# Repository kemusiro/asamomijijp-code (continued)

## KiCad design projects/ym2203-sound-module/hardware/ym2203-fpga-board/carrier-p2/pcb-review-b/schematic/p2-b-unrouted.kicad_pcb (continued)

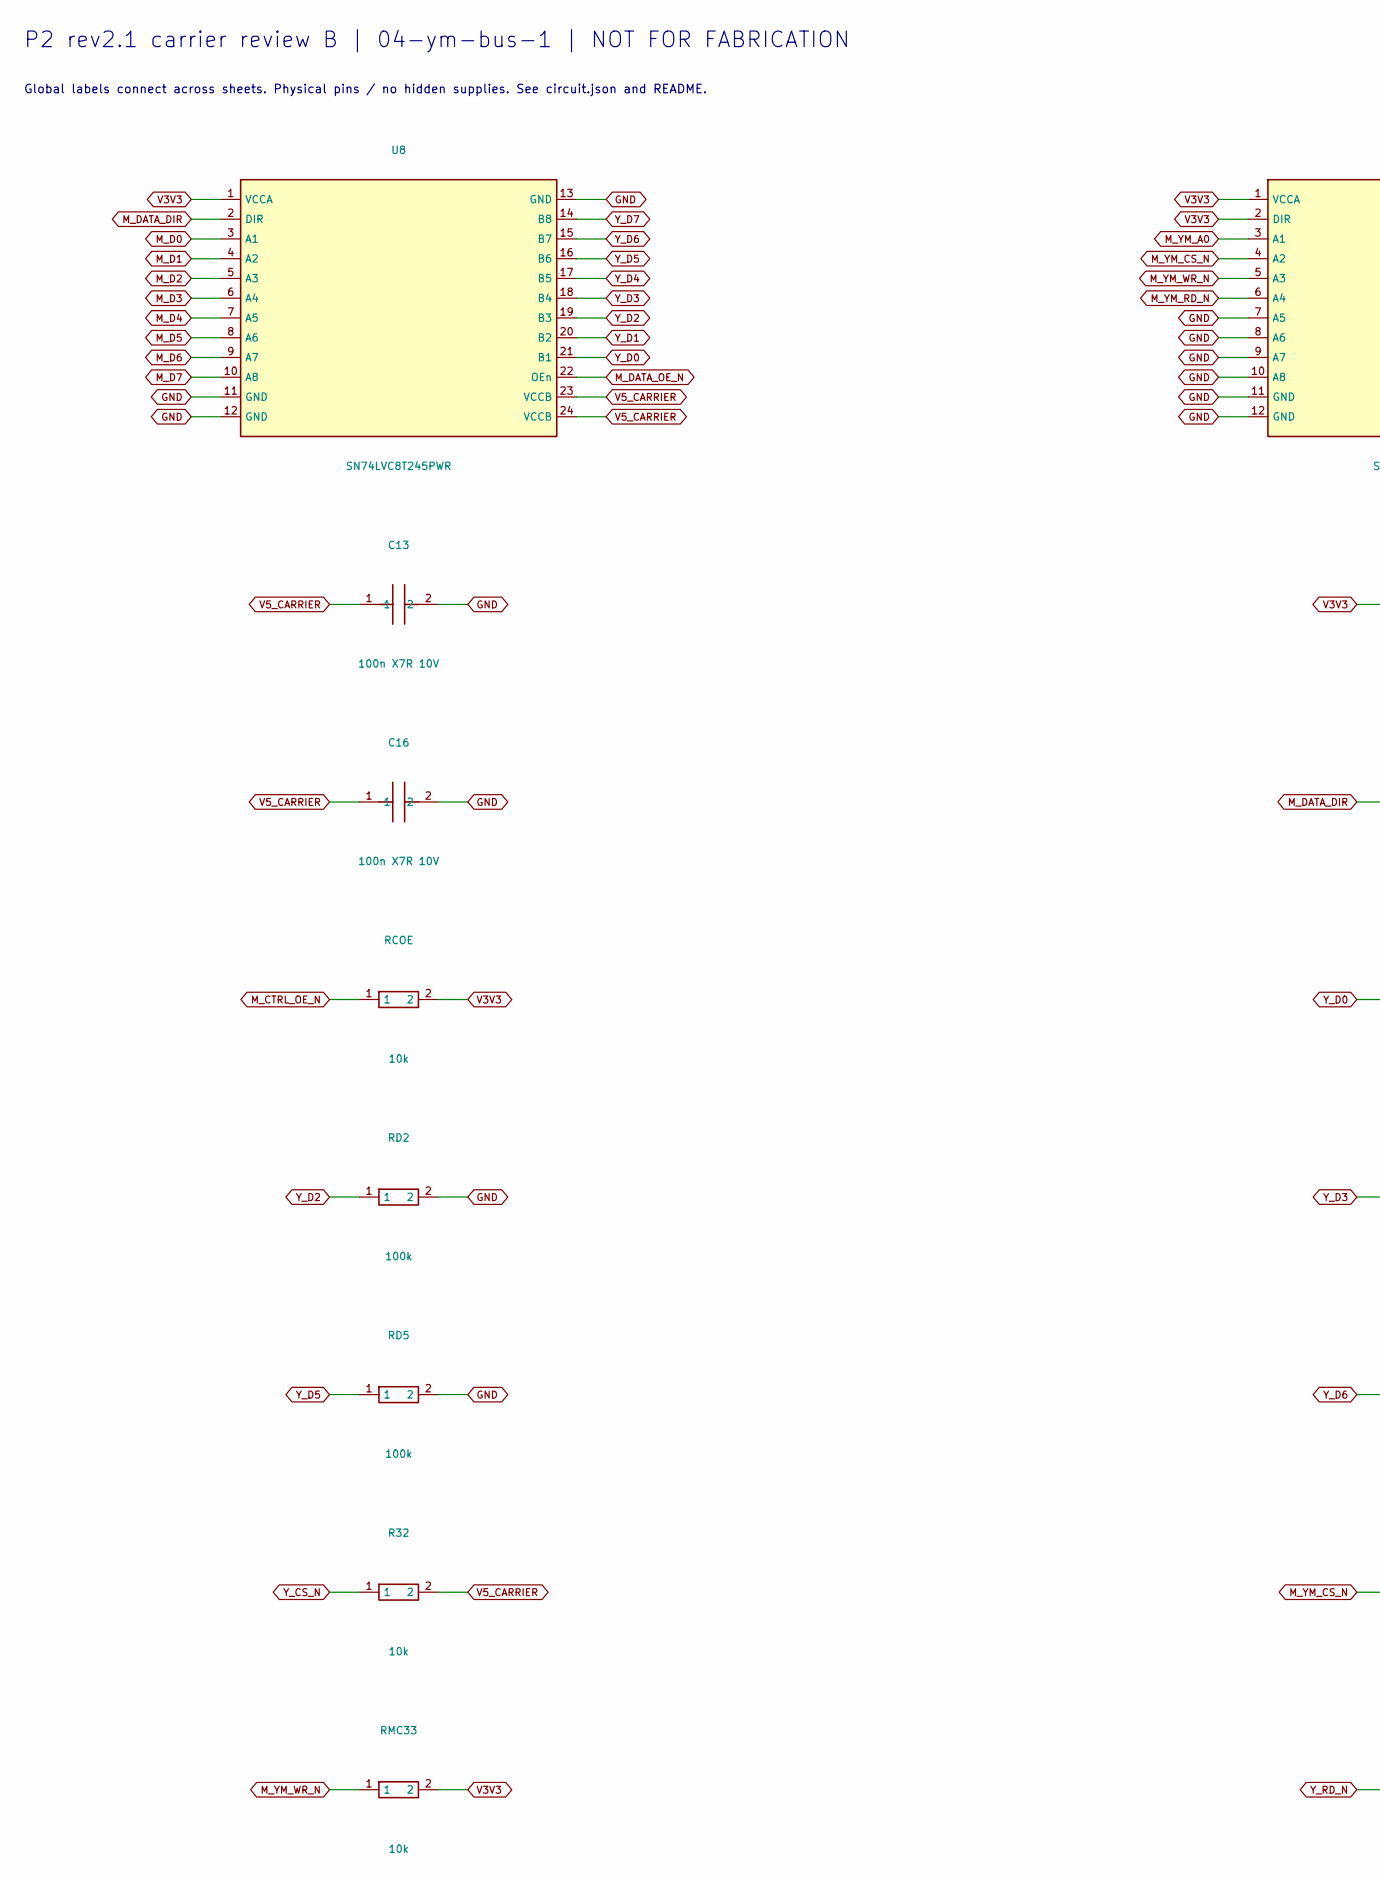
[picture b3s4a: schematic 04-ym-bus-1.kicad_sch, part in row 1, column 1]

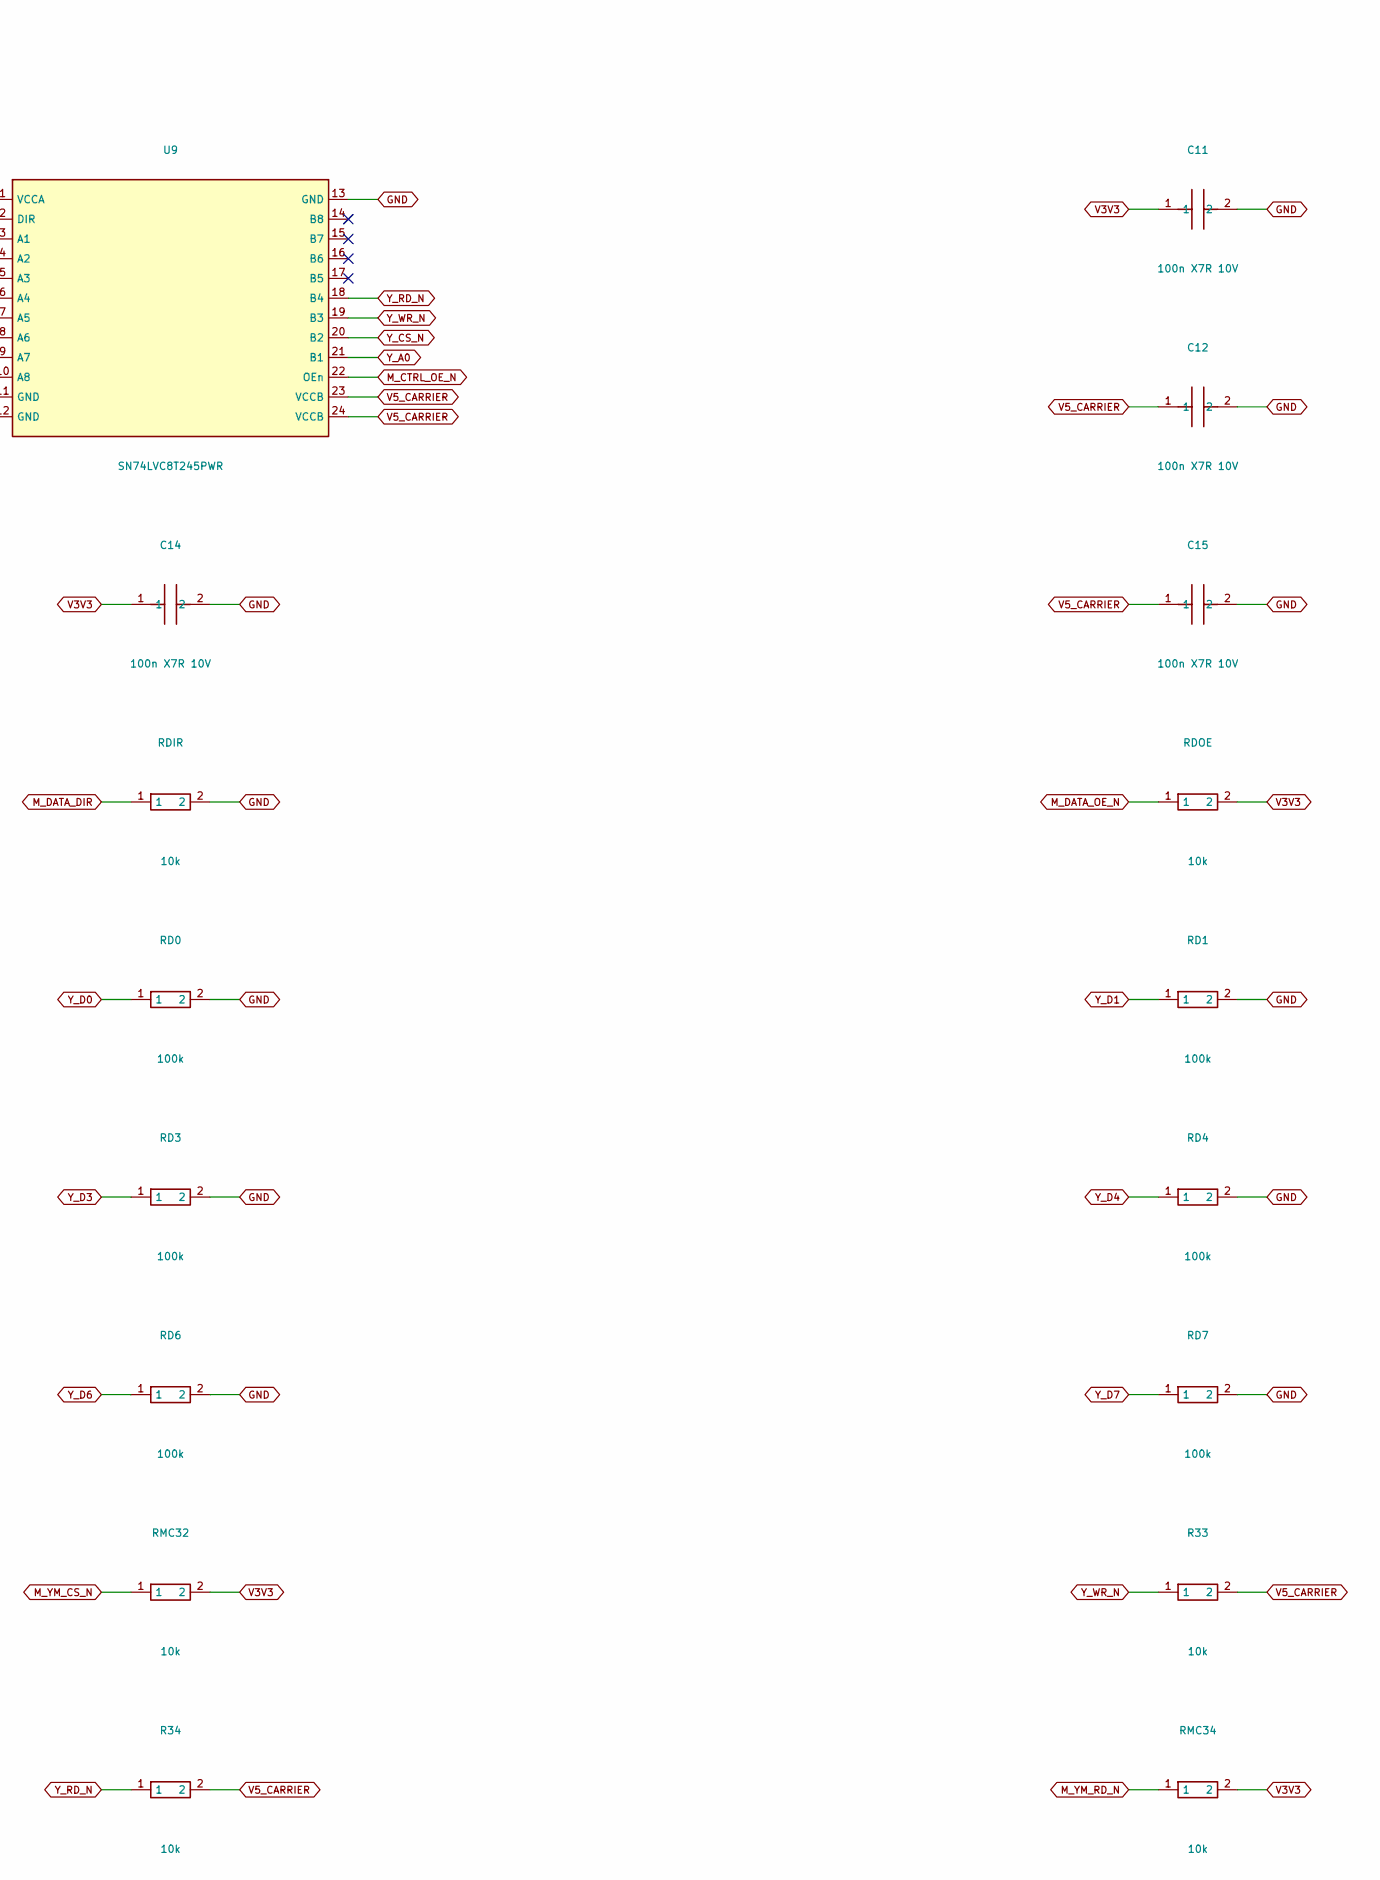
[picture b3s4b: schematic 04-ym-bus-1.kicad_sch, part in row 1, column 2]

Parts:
C11, C12, C13, C14, C15, C16: 100n X7R 10V; C_0805_2012Metric
R32, R33, R34: 10k; R_0805_2012Metric
RCOE: 10k; R_0805_2012Metric
RD0, RD1, RD2, RD3, RD4, RD5, RD6, RD7: 100k; R_0805_2012Metric
RDIR: 10k; R_0805_2012Metric
RDOE: 10k; R_0805_2012Metric
RMC32, RMC33, RMC34: 10k; R_0805_2012Metric
U8, U9: SN74LVC8T245PWR; TSSOP-24_4.4x7.8mm_P0.65mm

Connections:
GND: C11.2, C12.2, C13.2, C14.2, C15.2, C16.2, RD0.2, RD1.2, RD2.2, RD3.2, RD4.2, RD5.2, RD6.2, RD7.2, RDIR.2, U8.11 (GND), U8.12 (GND), U8.13 (GND), U9.7 (A5), U9.8 (A6), U9.9 (A7), U9.10 (A8), U9.11 (GND), U9.12 (GND), U9.13 (GND); also elsewhere on the board
M_CTRL_OE_N: RCOE.1, U9.22 (OEn); also elsewhere on the board
M_D0: U8.3 (A1); also elsewhere on the board
M_D1: U8.4 (A2); also elsewhere on the board
M_D2: U8.5 (A3); also elsewhere on the board
M_D3: U8.6 (A4); also elsewhere on the board
M_D4: U8.7 (A5); also elsewhere on the board
M_D5: U8.8 (A6); also elsewhere on the board
M_D6: U8.9 (A7); also elsewhere on the board
M_D7: U8.10 (A8); also elsewhere on the board
M_DATA_DIR: RDIR.1, U8.2 (DIR); also elsewhere on the board
M_DATA_OE_N: RDOE.1, U8.22 (OEn); also elsewhere on the board
M_YM_A0: U9.3 (A1); also elsewhere on the board
M_YM_CS_N: RMC32.1, U9.4 (A2); also elsewhere on the board
M_YM_RD_N: RMC34.1, U9.6 (A4); also elsewhere on the board
M_YM_WR_N: RMC33.1, U9.5 (A3); also elsewhere on the board
V3V3: C11.1, C14.1, RCOE.2, RDOE.2, RMC32.2, RMC33.2, RMC34.2, U8.1 (VCCA), U9.1 (VCCA), U9.2 (DIR); also elsewhere on the board
V5_CARRIER: C12.1, C13.1, C15.1, C16.1, R32.2, R33.2, R34.2, U8.23 (VCCB), U8.24 (VCCB), U9.23 (VCCB), U9.24 (VCCB); also elsewhere on the board
Y_A0: U9.21 (B1); also elsewhere on the board
Y_CS_N: R32.1, U9.20 (B2); also elsewhere on the board
Y_D0: RD0.1, U8.21 (B1); also elsewhere on the board
Y_D1: RD1.1, U8.20 (B2); also elsewhere on the board
Y_D2: RD2.1, U8.19 (B3); also elsewhere on the board
Y_D3: RD3.1, U8.18 (B4); also elsewhere on the board
Y_D4: RD4.1, U8.17 (B5); also elsewhere on the board
Y_D5: RD5.1, U8.16 (B6); also elsewhere on the board
Y_D6: RD6.1, U8.15 (B7); also elsewhere on the board
Y_D7: RD7.1, U8.14 (B8); also elsewhere on the board
Y_RD_N: R34.1, U9.18 (B4); also elsewhere on the board
Y_WR_N: R33.1, U9.19 (B3); also elsewhere on the board

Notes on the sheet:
P2 rev2.1 carrier review B | 04-ym-bus-1 | NOT FOR FABRICATION
Global labels connect across sheets. Physical pins / no hidden supplies. See circuit.json and README.

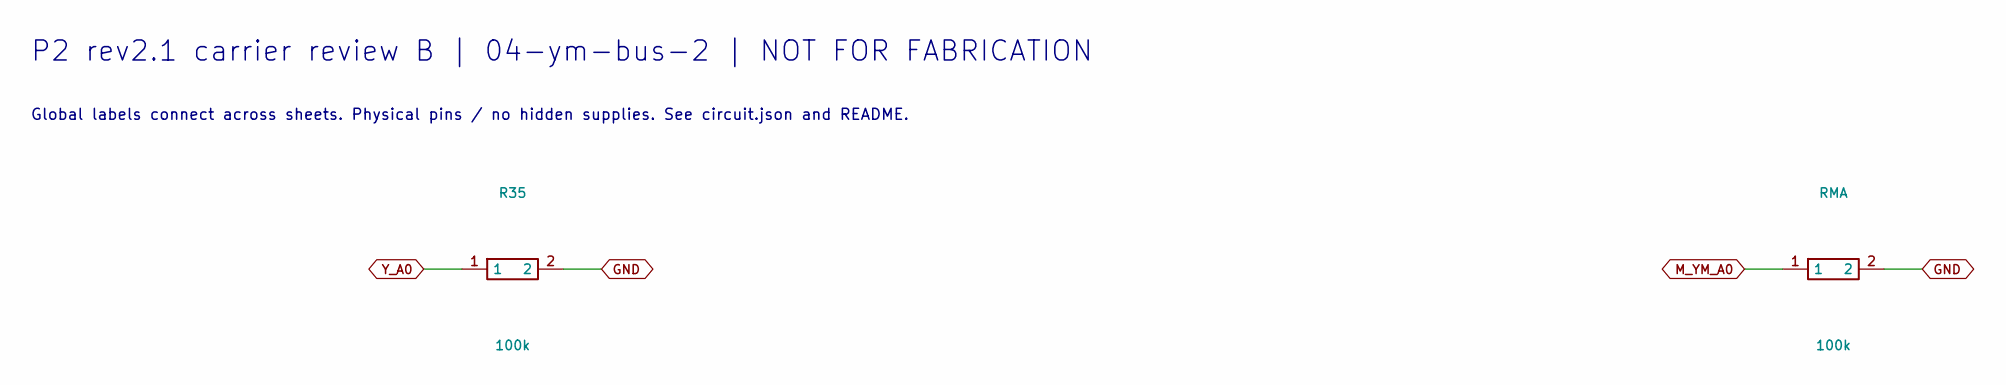
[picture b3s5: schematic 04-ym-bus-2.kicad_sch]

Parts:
R35: 100k; R_0805_2012Metric
RMA: 100k; R_0805_2012Metric

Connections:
GND: R35.2, RMA.2; also elsewhere on the board
M_YM_A0: RMA.1; also elsewhere on the board
Y_A0: R35.1; also elsewhere on the board

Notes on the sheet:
P2 rev2.1 carrier review B | 04-ym-bus-2 | NOT FOR FABRICATION
Global labels connect across sheets. Physical pins / no hidden supplies. See circuit.json and README.

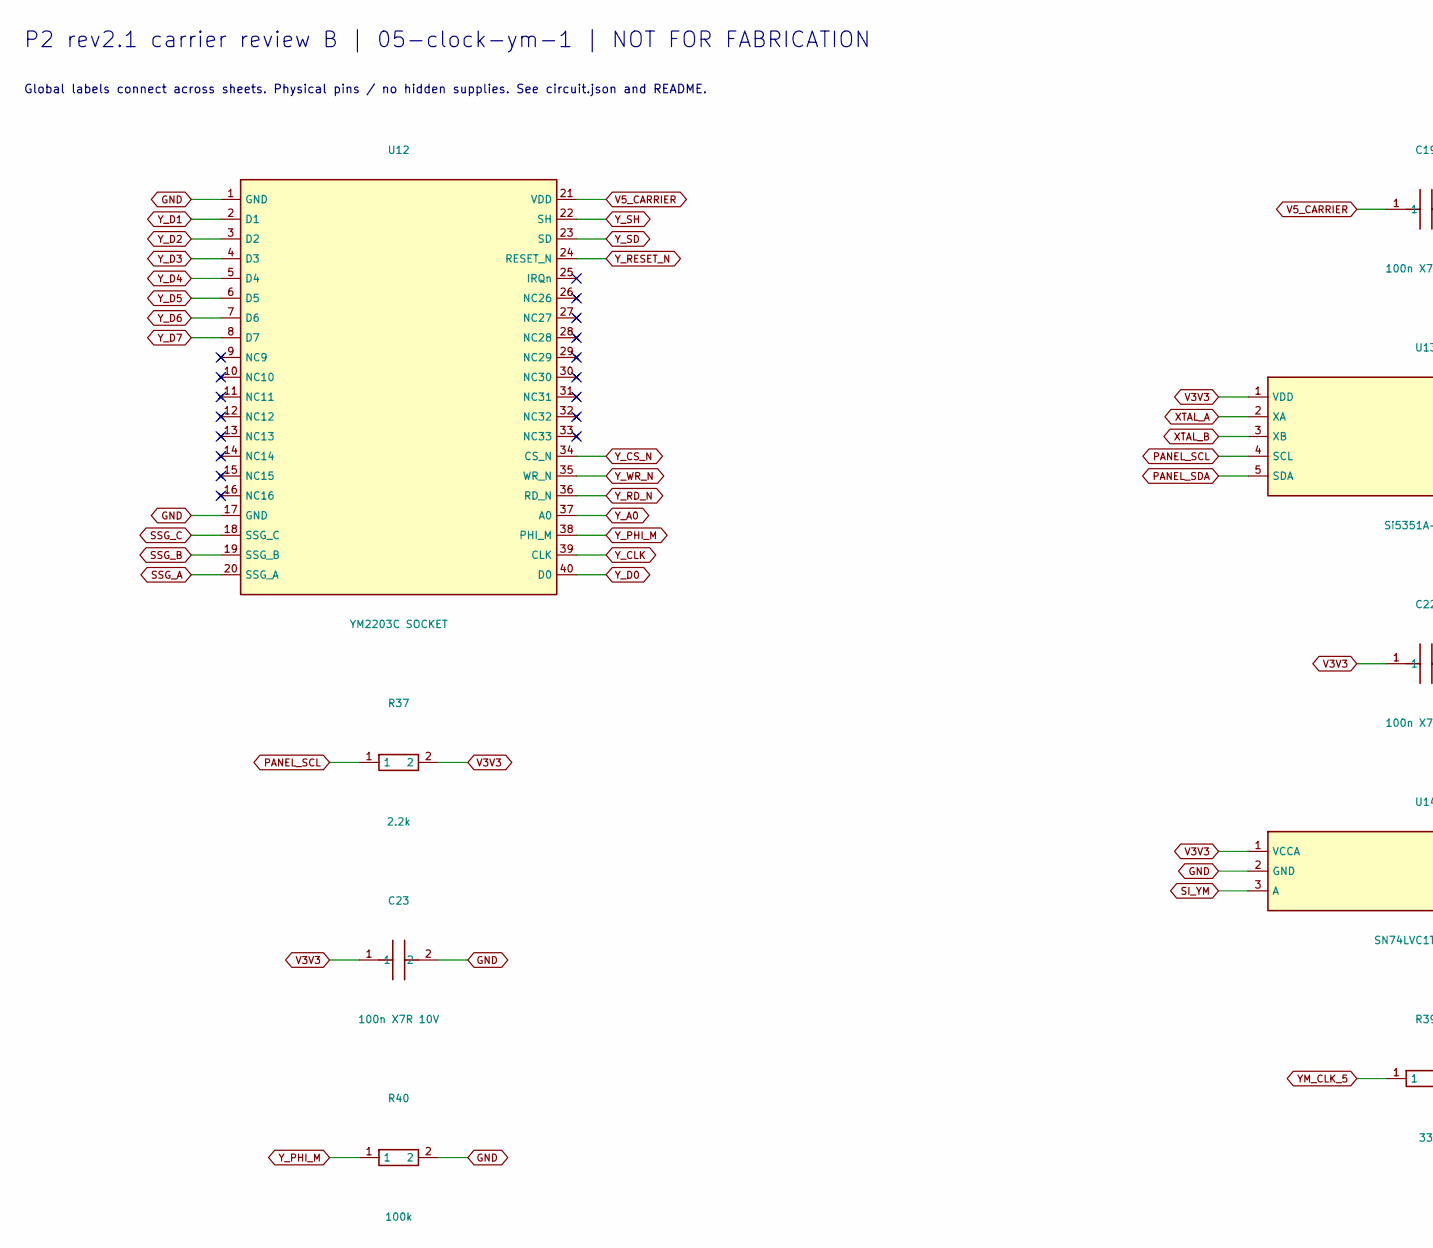
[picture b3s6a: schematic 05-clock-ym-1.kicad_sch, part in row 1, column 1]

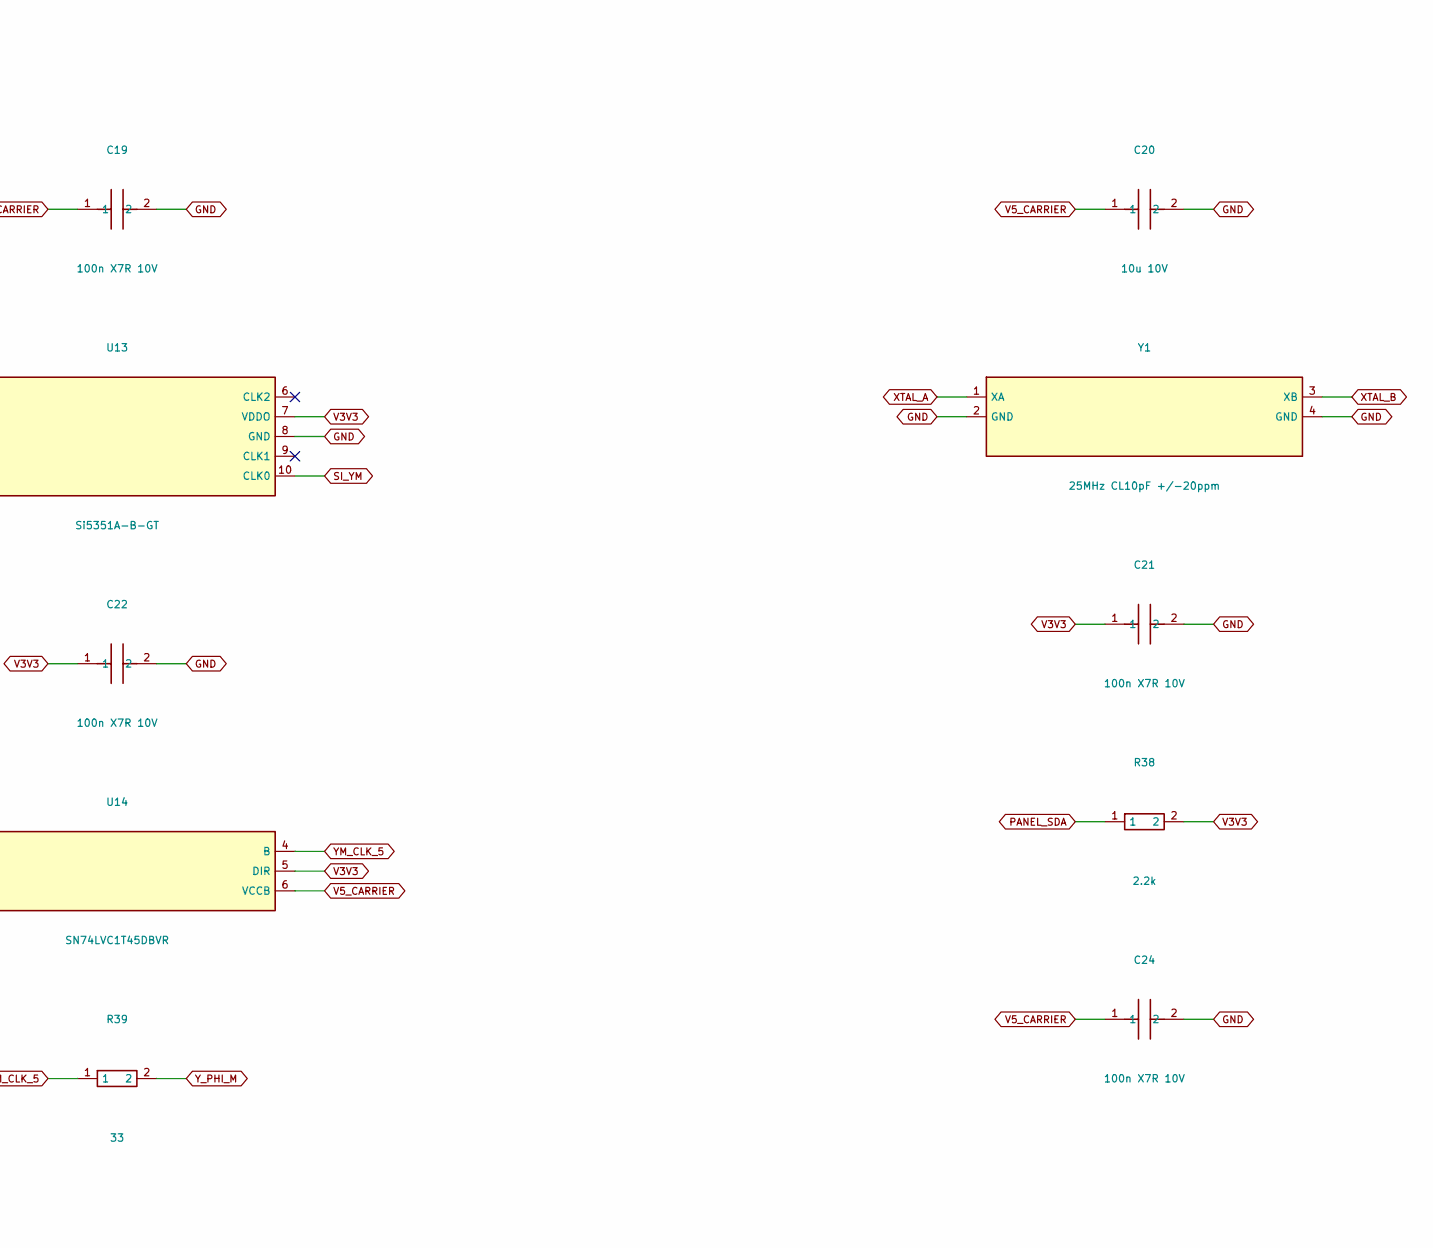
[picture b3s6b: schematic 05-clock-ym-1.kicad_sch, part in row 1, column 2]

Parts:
C19, C21, C22, C23, C24: 100n X7R 10V; C_0805_2012Metric
C20: 10u 10V; C_0805_2012Metric
R37, R38: 2.2k; R_0805_2012Metric
R39: 33; R_0805_2012Metric
R40: 100k; R_0805_2012Metric
U12: YM2203C SOCKET; DIP-40_W15.24mm_Socket
U13: Si5351A-B-GT; MSOP-10_3x3mm_P0.5mm
U14: SN74LVC1T45DBVR; SOT-23-6
Y1: 25MHz CL10pF +/-20ppm; Crystal_SMD_3225-4Pin_3.2x2.5mm

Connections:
GND: C19.2, C20.2, C21.2, C22.2, C23.2, C24.2, R40.2, U12.1 (GND), U12.17 (GND), U13.8 (GND), U14.2 (GND), Y1.2 (GND), Y1.4 (GND); also elsewhere on the board
PANEL_SCL: R37.1, U13.4 (SCL); also elsewhere on the board
PANEL_SDA: R38.1, U13.5 (SDA); also elsewhere on the board
SI_YM: U13.10 (CLK0), U14.3 (A)
SSG_A: U12.20 (SSG_A); also elsewhere on the board
SSG_B: U12.19 (SSG_B); also elsewhere on the board
SSG_C: U12.18 (SSG_C); also elsewhere on the board
V3V3: C21.1, C22.1, C23.1, R37.2, R38.2, U13.1 (VDD), U13.7 (VDDO), U14.1 (VCCA), U14.5 (DIR); also elsewhere on the board
V5_CARRIER: C19.1, C20.1, C24.1, U12.21 (VDD), U14.6 (VCCB); also elsewhere on the board
XTAL_A: U13.2 (XA), Y1.1 (XA)
XTAL_B: U13.3 (XB), Y1.3 (XB)
YM_CLK_5: R39.1, U14.4 (B)
Y_A0: U12.37 (A0); also elsewhere on the board
Y_CLK: U12.39 (CLK); also elsewhere on the board
Y_CS_N: U12.34 (CS_N); also elsewhere on the board
Y_D0: U12.40 (D0); also elsewhere on the board
Y_D1: U12.2 (D1); also elsewhere on the board
Y_D2: U12.3 (D2); also elsewhere on the board
Y_D3: U12.4 (D3); also elsewhere on the board
Y_D4: U12.5 (D4); also elsewhere on the board
Y_D5: U12.6 (D5); also elsewhere on the board
Y_D6: U12.7 (D6); also elsewhere on the board
Y_D7: U12.8 (D7); also elsewhere on the board
Y_PHI_M: R39.2, R40.1, U12.38 (PHI_M)
Y_RD_N: U12.36 (RD_N); also elsewhere on the board
Y_RESET_N: U12.24 (RESET_N); also elsewhere on the board
Y_SD: U12.23 (SD); also elsewhere on the board
Y_SH: U12.22 (SH); also elsewhere on the board
Y_WR_N: U12.35 (WR_N); also elsewhere on the board

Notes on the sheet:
P2 rev2.1 carrier review B | 05-clock-ym-1 | NOT FOR FABRICATION
Global labels connect across sheets. Physical pins / no hidden supplies. See circuit.json and README.

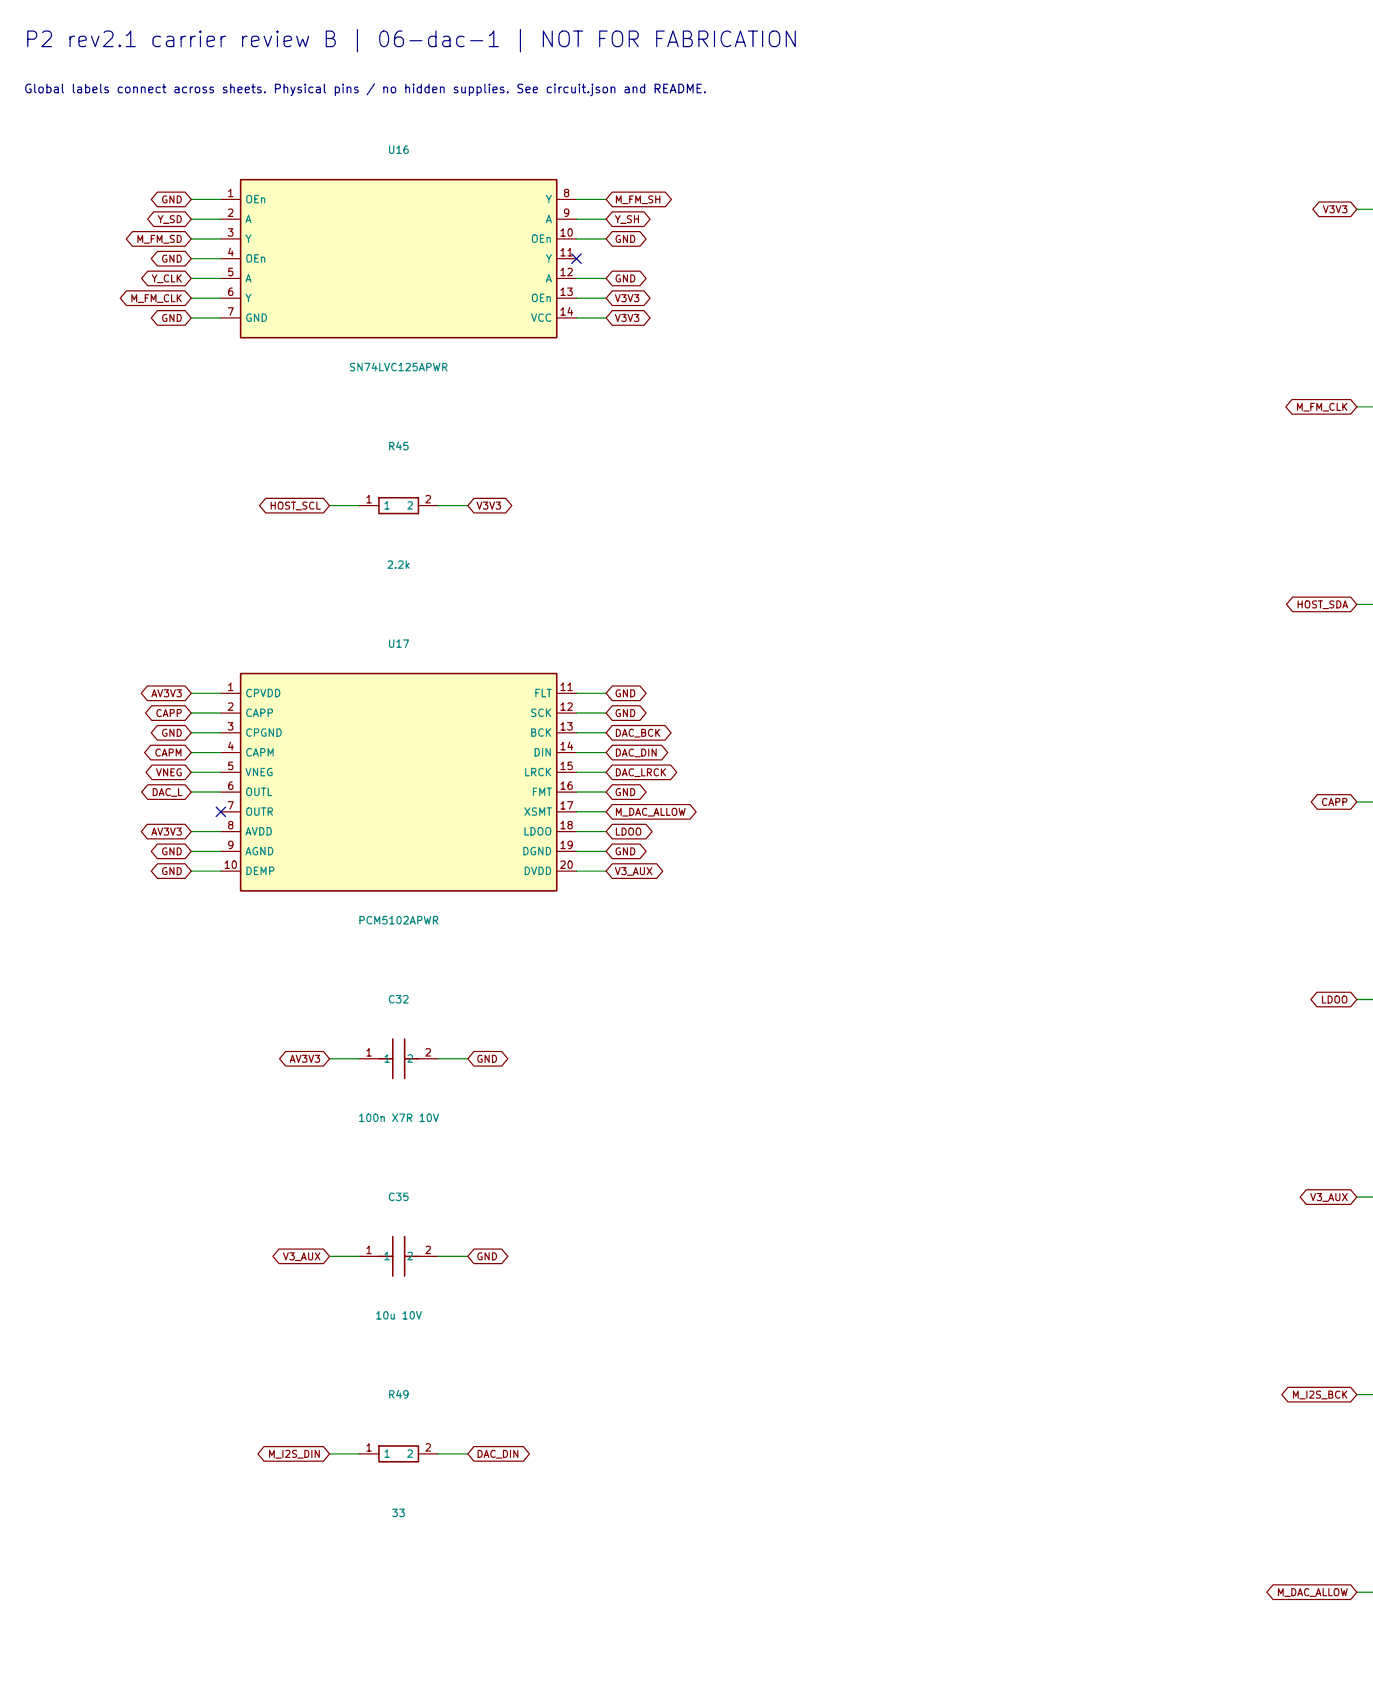
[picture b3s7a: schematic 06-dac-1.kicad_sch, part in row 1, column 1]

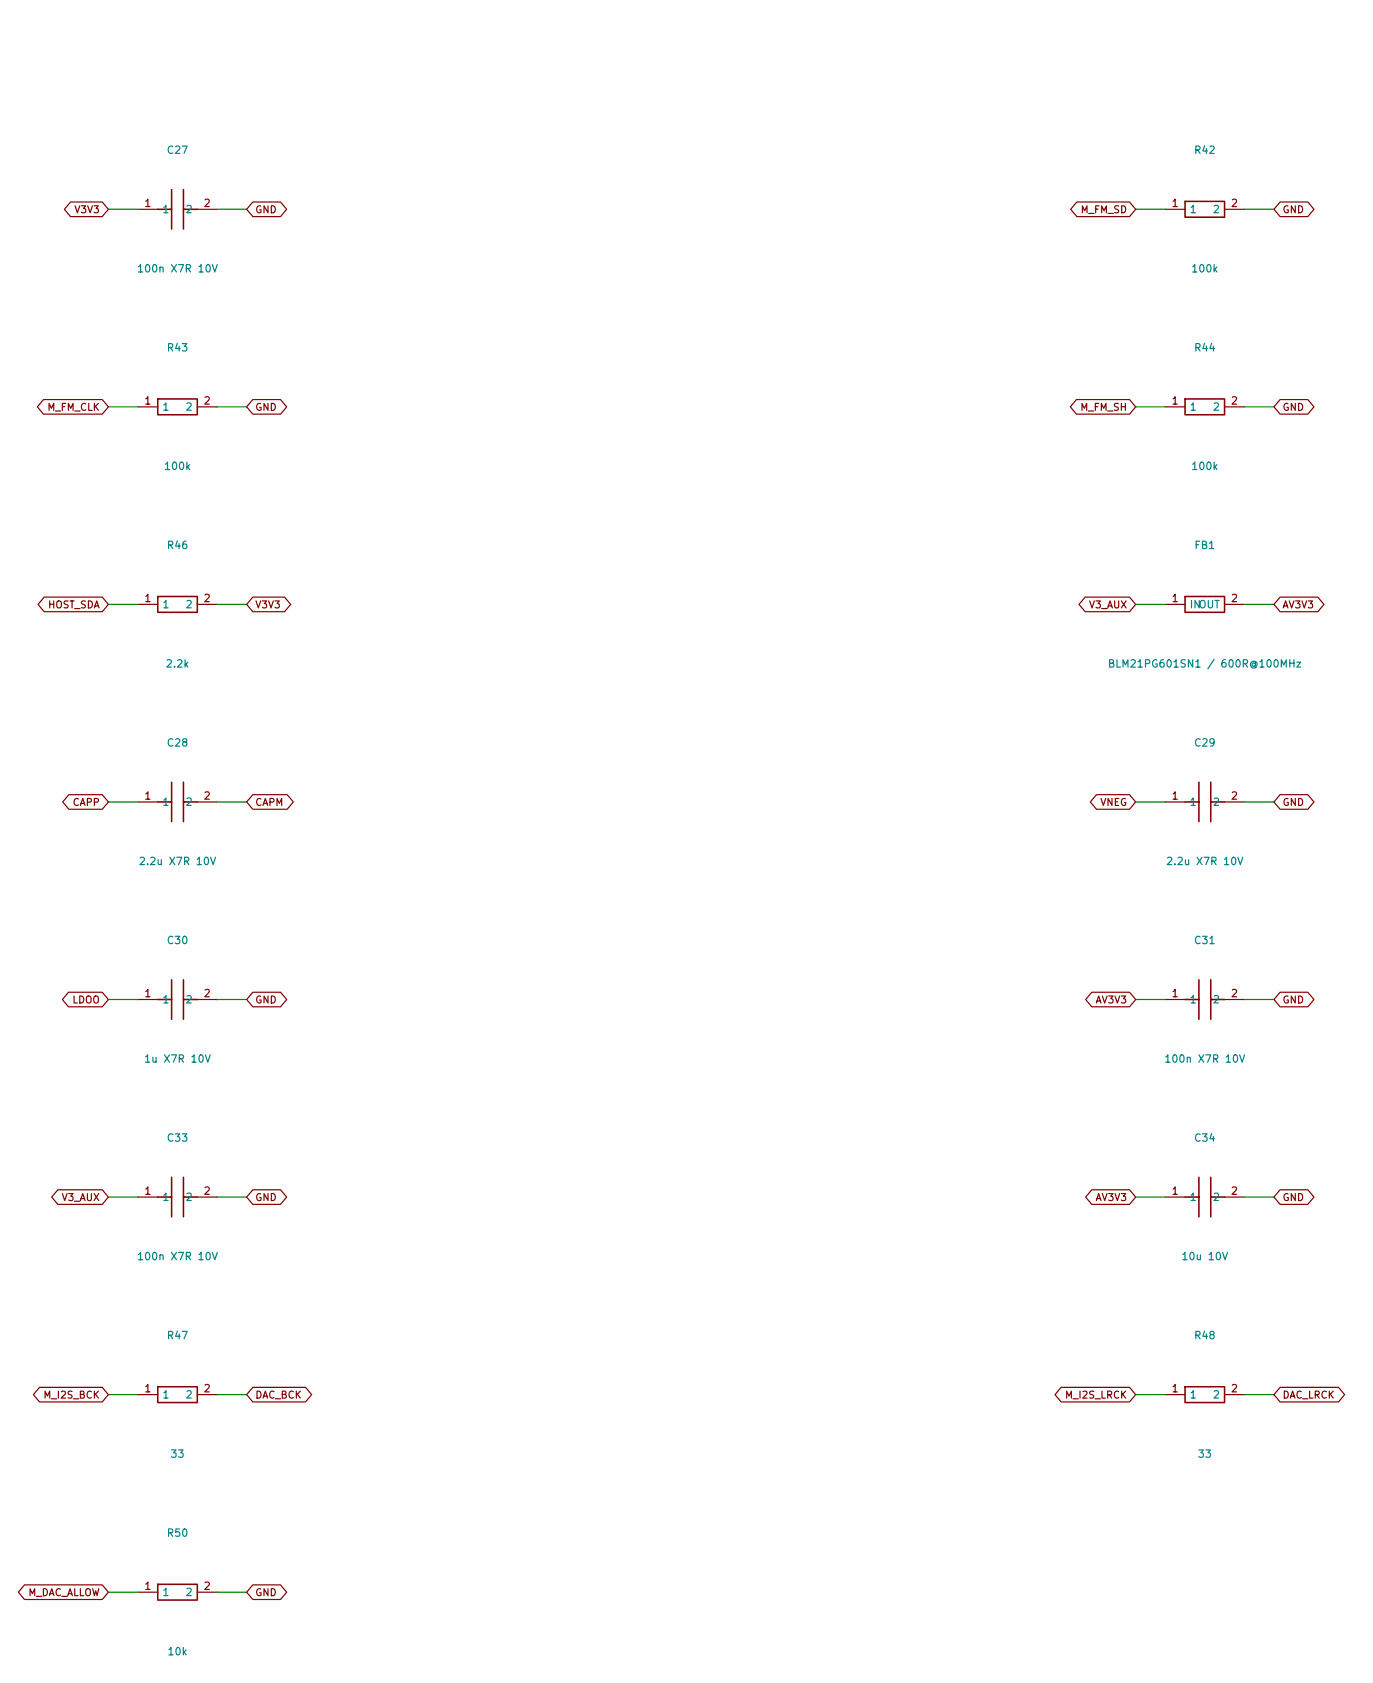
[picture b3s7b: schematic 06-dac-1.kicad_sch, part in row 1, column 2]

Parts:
C27, C31, C32, C33: 100n X7R 10V; C_0805_2012Metric
C28, C29: 2.2u X7R 10V; C_0805_2012Metric
C30: 1u X7R 10V; C_0805_2012Metric
C34, C35: 10u 10V; C_0805_2012Metric
FB1: BLM21PG601SN1 / 600R@100MHz; L_0805_2012Metric
R42, R43, R44: 100k; R_0805_2012Metric
R45, R46: 2.2k; R_0805_2012Metric
R47, R48, R49: 33; R_0805_2012Metric
R50: 10k; R_0805_2012Metric
U16: SN74LVC125APWR; TSSOP-14_4.4x5mm_P0.65mm
U17: PCM5102APWR; TSSOP-20_4.4x6.5mm_P0.65mm

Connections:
AV3V3: C31.1, C32.1, C34.1, FB1.2 (OUT), U17.1 (CPVDD), U17.8 (AVDD)
CAPM: C28.2, U17.4 (CAPM)
CAPP: C28.1, U17.2 (CAPP)
DAC_BCK: R47.2, U17.13 (BCK); also elsewhere on the board
DAC_DIN: R49.2, U17.14 (DIN); also elsewhere on the board
DAC_L: U17.6 (OUTL); also elsewhere on the board
DAC_LRCK: R48.2, U17.15 (LRCK); also elsewhere on the board
GND: C27.2, C29.2, C30.2, C31.2, C32.2, C33.2, C34.2, C35.2, R42.2, R43.2, R44.2, R50.2, U16.1 (OEn), U16.4 (OEn), U16.7 (GND), U16.10 (OEn), U16.12 (A), U17.3 (CPGND), U17.9 (AGND), U17.10 (DEMP), U17.11 (FLT), U17.12 (SCK), U17.16 (FMT), U17.19 (DGND); also elsewhere on the board
HOST_SCL: R45.1; also elsewhere on the board
HOST_SDA: R46.1; also elsewhere on the board
LDOO: C30.1, U17.18 (LDOO)
M_DAC_ALLOW: R50.1, U17.17 (XSMT); also elsewhere on the board
M_FM_CLK: R43.1, U16.6 (Y); also elsewhere on the board
M_FM_SD: R42.1, U16.3 (Y); also elsewhere on the board
M_FM_SH: R44.1, U16.8 (Y); also elsewhere on the board
M_I2S_BCK: R47.1; also elsewhere on the board
M_I2S_DIN: R49.1; also elsewhere on the board
M_I2S_LRCK: R48.1; also elsewhere on the board
V3V3: C27.1, R45.2, R46.2, U16.13 (OEn), U16.14 (VCC); also elsewhere on the board
V3_AUX: C33.1, C35.1, FB1.1 (IN), U17.20 (DVDD); also elsewhere on the board
VNEG: C29.1, U17.5 (VNEG)
Y_CLK: U16.5 (A); also elsewhere on the board
Y_SD: U16.2 (A); also elsewhere on the board
Y_SH: U16.9 (A); also elsewhere on the board

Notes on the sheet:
P2 rev2.1 carrier review B | 06-dac-1 | NOT FOR FABRICATION
Global labels connect across sheets. Physical pins / no hidden supplies. See circuit.json and README.
